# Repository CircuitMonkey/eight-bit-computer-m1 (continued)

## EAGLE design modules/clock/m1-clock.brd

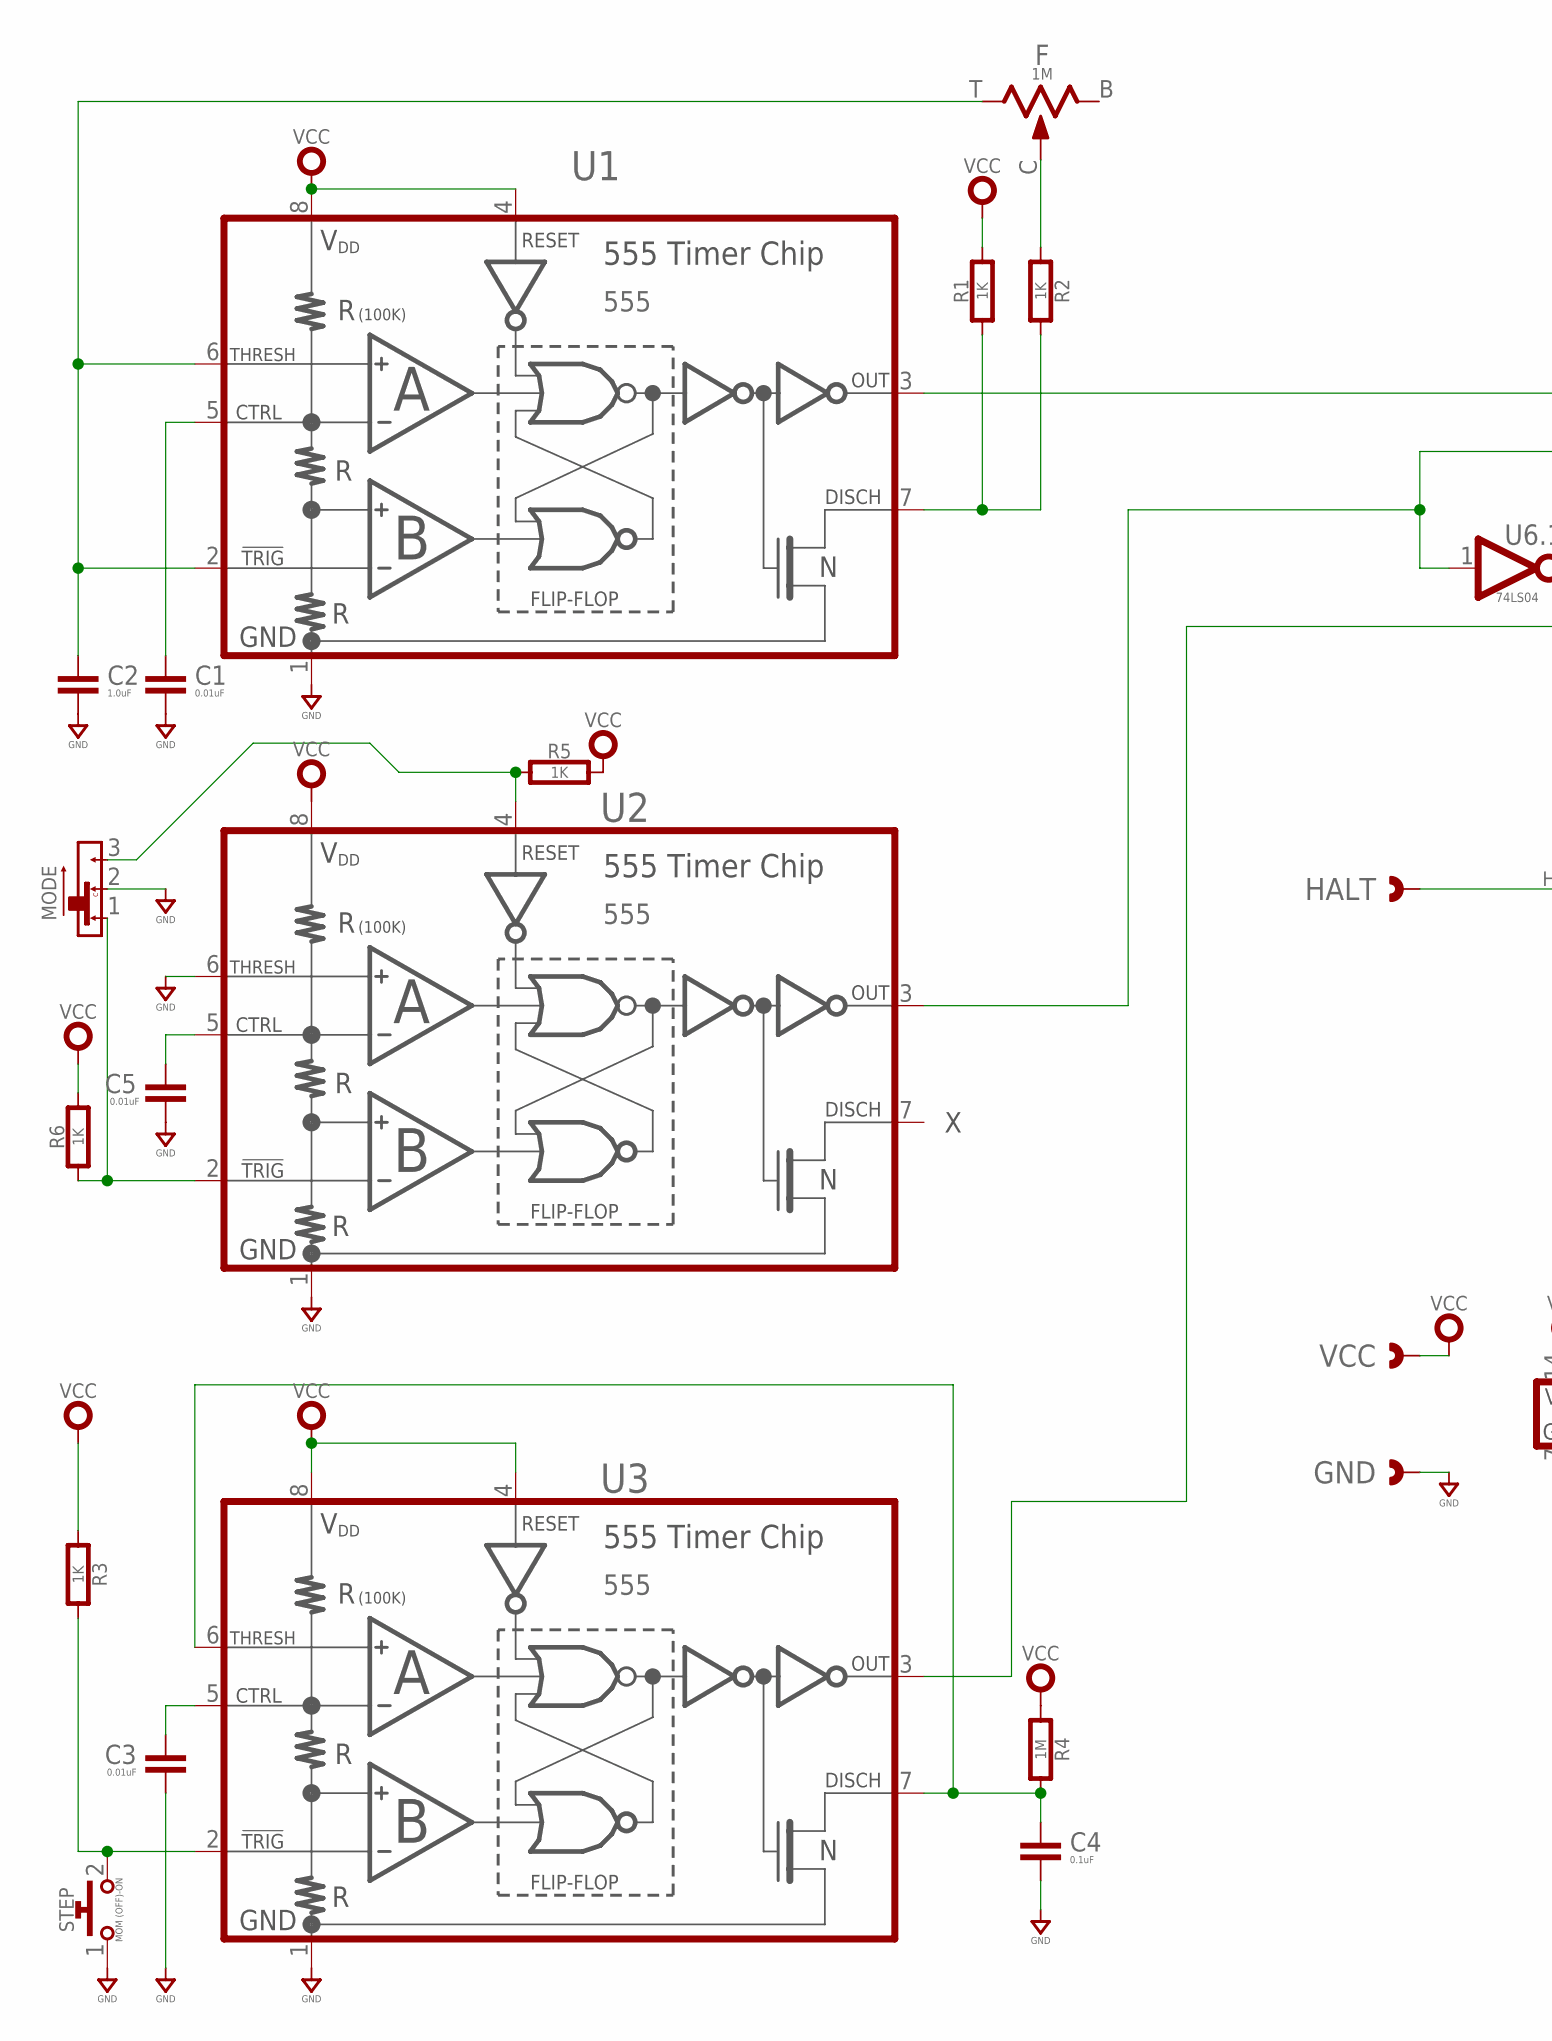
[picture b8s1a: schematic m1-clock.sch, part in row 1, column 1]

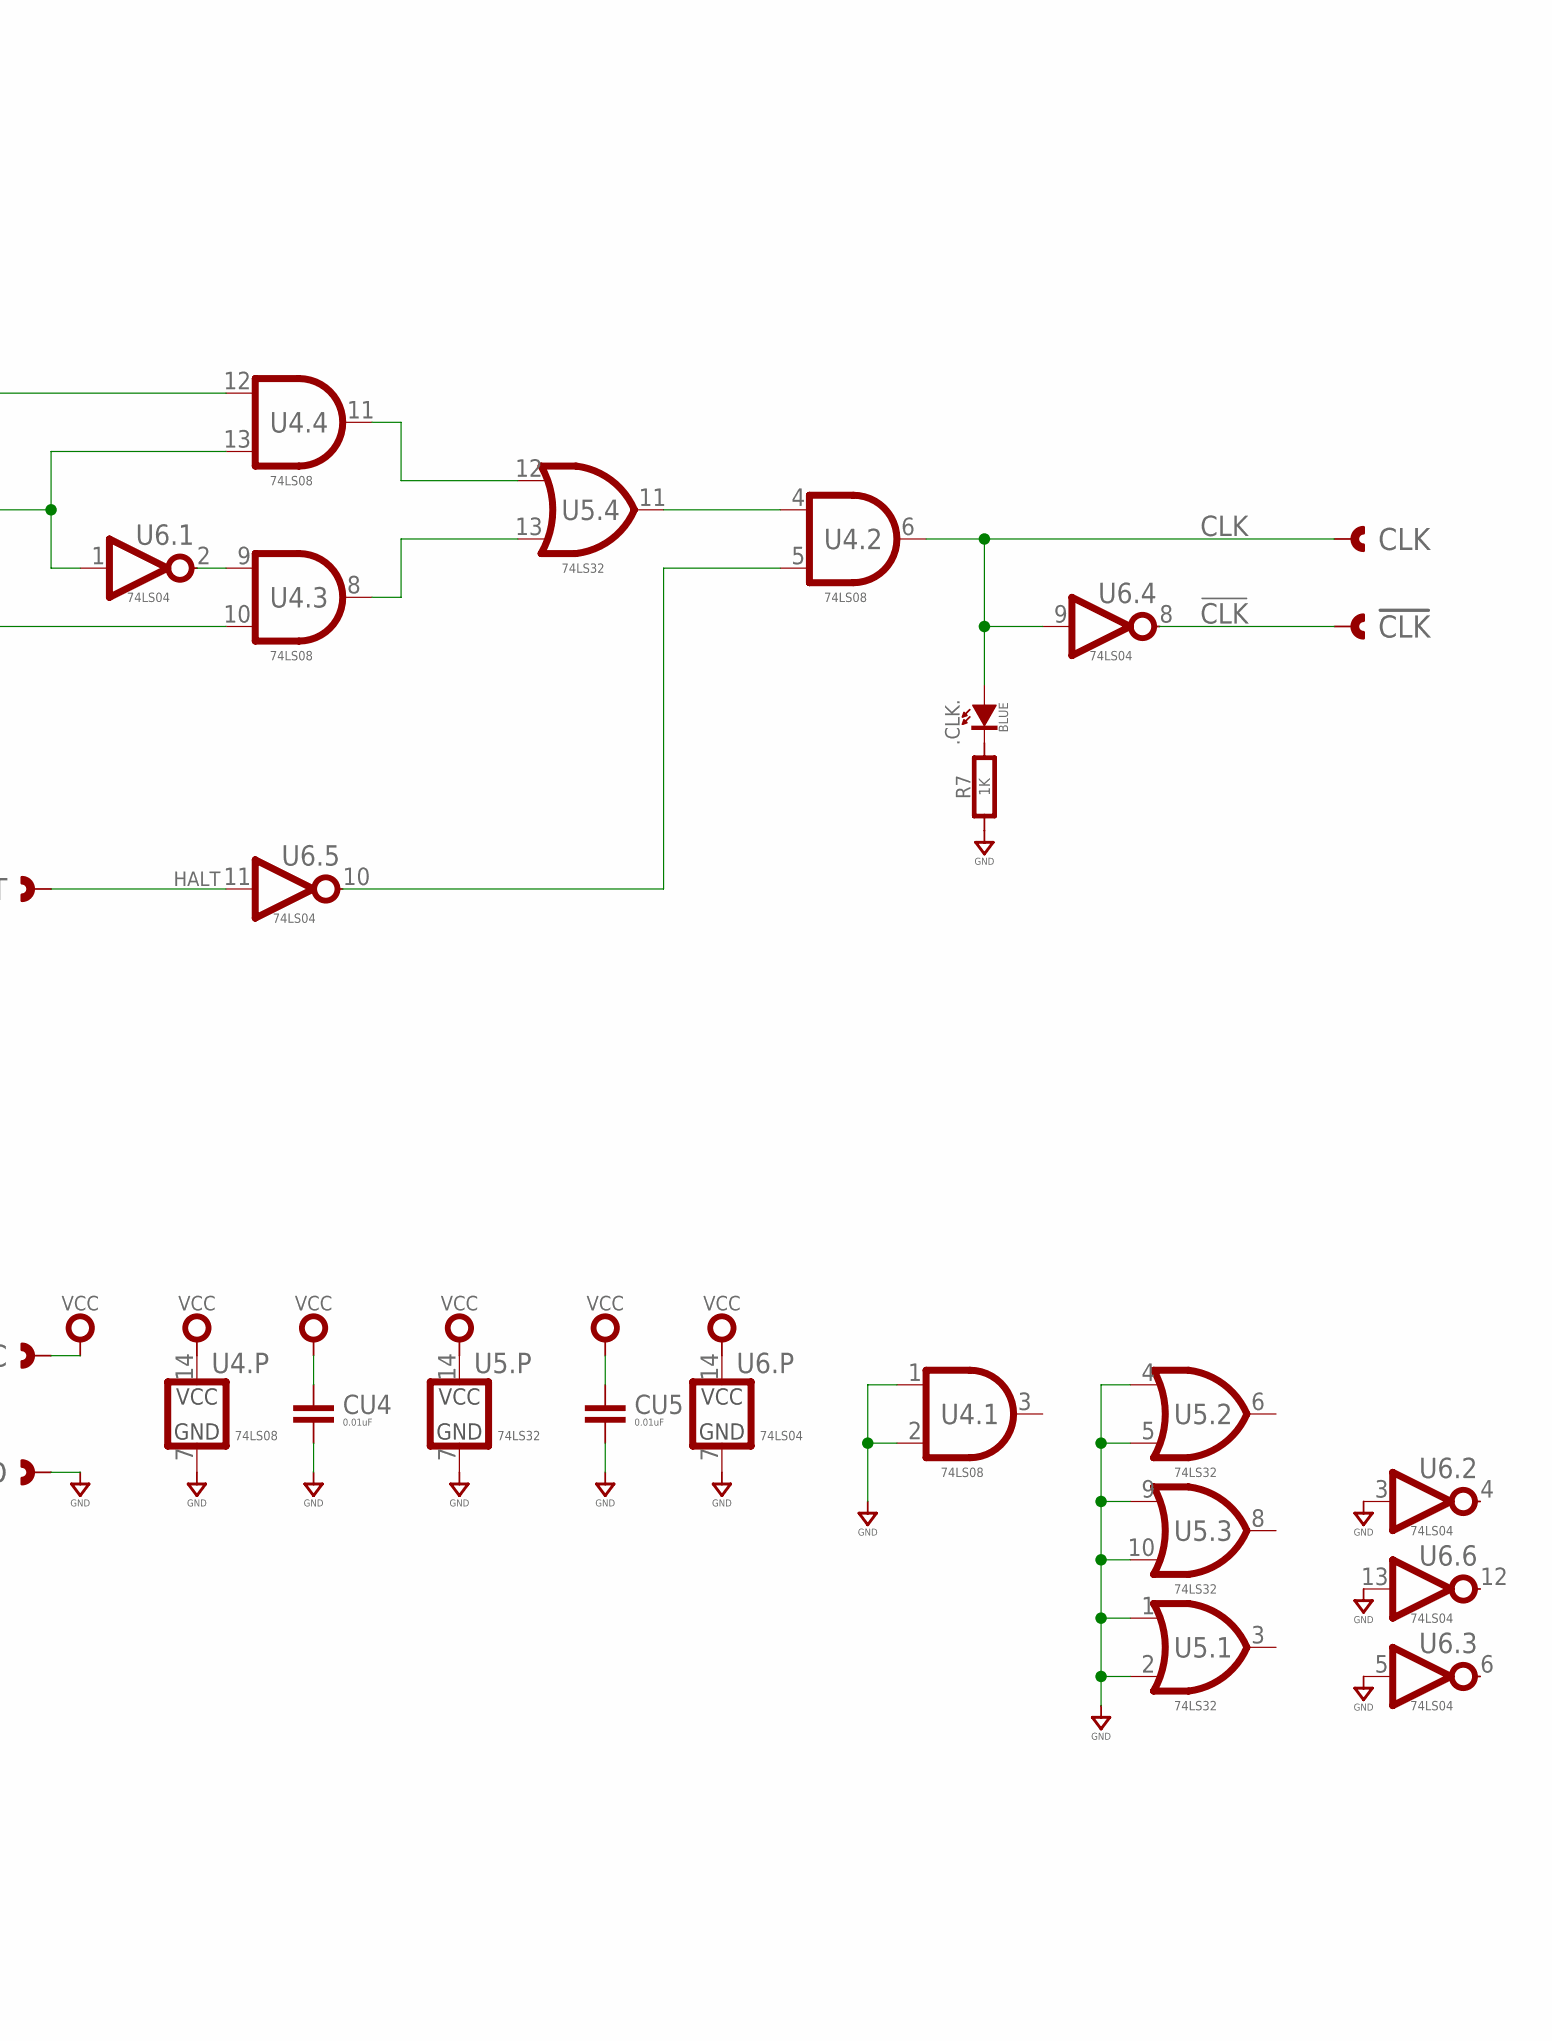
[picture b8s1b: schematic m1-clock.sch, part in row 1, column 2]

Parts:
!CLK: CAST-01X1; CAST01-2.54MM
.CLK.: BLUE; SMD_0603
C1, C3, C5: 0.01uF; 0603-CAP
C2: 1.0uF; 0603-CAP
C4: 0.1uF; 0603-CAP
CLK: CAST-01X1; CAST01-2.54MM
CU4, CU5: 0.01uF; 0603-CAP
F: 1M; TRIM_BOURNS_TC33X
GND: CAST-01X1; CAST01-2.54MM
HALT: CAST-01X1; CAST01-2.54MM
MODE: SLIDE-SPDTJS102011JCQN; CK_JS102011JCQN
R1, R2, R3, R5, R6, R7: 1K; 0603-RES
R4: 1M; 0603-RES
STEP: MOM (OFF)-ON; SWITCH-0635-2P-SMD
U1, U2, U3: 555; SOP08
U4: 74LS08; SOP14
U5: 74LS32; SOP14
U6: 74LS04; SOP14
VCC: CAST-01X1; CAST01-2.54MM

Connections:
!CLK: !CLK.1, U6.8 (Y)
CLK: .CLK..A, CLK.1, U4.6 (Y), U6.9 (A)
GND: C1.2, C2.2, C3.2, C4.2, C5.2, CU4.2, CU5.2, GND.1, MODE.2, R7.2, STEP.1, U1.1 (GND), U2.1 (GND), U2.6 (THRESHOLD), U3.1 (GND), U4.1 (A), U4.2 (B), U4.7 (GND), U5.1 (A), U5.2 (B), U5.4 (A), U5.5 (B), U5.7 (GND), U5.9 (A), U5.10 (B), U6.3 (A), U6.5 (A), U6.7 (GND), U6.13 (A)
HALT: HALT.1, U6.11 (A)
unnamed: C1.1, U1.5 (CONTROL)
unnamed: C2.1, F.T (3), U1.2 (TRIGGER#), U1.6 (THRESHOLD)
unnamed: U1.3 (OUTPUT), U4.12 (A)
unnamed: R1.1, R2.2, U1.7 (DISCHARGE)
unnamed: F.C (2), R2.1
unnamed: C3.1, U3.5 (CONTROL)
unnamed: R3.2, STEP.2, U3.2 (TRIGGER#)
unnamed: U3.3 (OUTPUT), U4.10 (B)
unnamed: MODE.3, R5.1, U2.4 (RESET#)
unnamed: C4.1, R4.2, U3.6 (THRESHOLD), U3.7 (DISCHARGE)
unnamed: MODE.1, R6.1, U2.2 (TRIGGER#)
unnamed: C5.1, U2.5 (CONTROL)
unnamed: U4.9 (A), U6.2 (Y)
unnamed: U2.3 (OUTPUT), U4.13 (B), U6.1 (A)
unnamed: U4.11 (Y), U5.12 (A)
unnamed: U4.8 (Y), U5.13 (B)
unnamed: U4.4 (A), U5.11 (Y)
unnamed: U4.5 (B), U6.10 (Y)
unnamed: .CLK..K (C), R7.1
VCC: CU4.1, CU5.1, R1.2, R3.1, R4.1, R5.2, R6.2, U1.4 (RESET#), U1.8 (VDD), U2.8 (VDD), U3.4 (RESET#), U3.8 (VDD), U4.14 (VCC), U5.14 (VCC), U6.14 (VCC), VCC.1

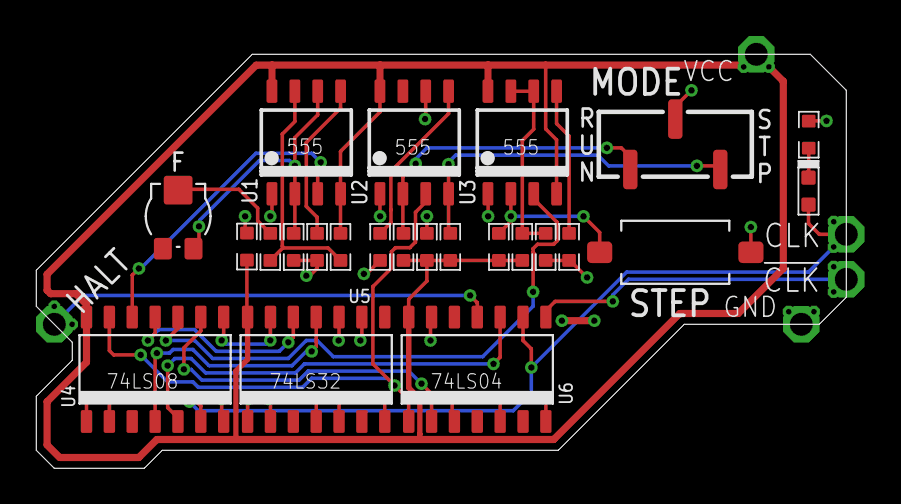
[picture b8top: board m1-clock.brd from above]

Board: 2 copper layers, 45.0 x 23.0 mm, 29 parts (0 on the bottom side), 24 nets.

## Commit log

2020-04-13 Progress checkin
    Centerplane, Output . register and clock board fabricted.
    Output board has REDLINE notes.
2021-07-29 Various updates
